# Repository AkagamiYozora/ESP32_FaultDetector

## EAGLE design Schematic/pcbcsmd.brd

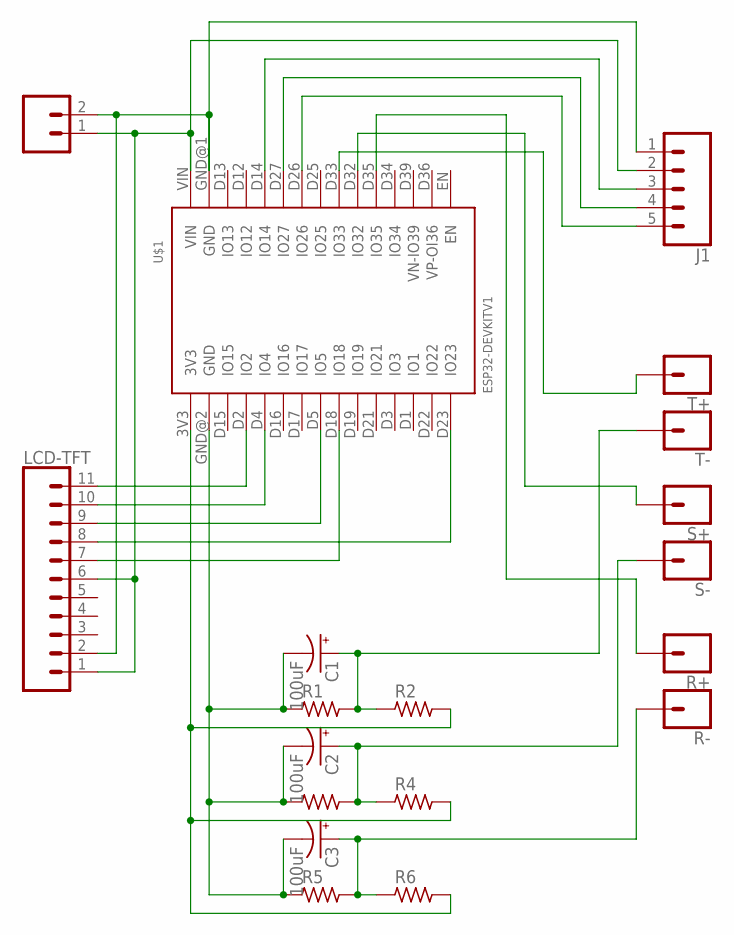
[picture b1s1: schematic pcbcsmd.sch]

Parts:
C1, C2, C3: 100uF; PANASONIC_D
J1: CONN_05; 1X05
LCD-TFT: CONN_11; 1X11
POWER: CONN_02; 1X02
R1, R2, R3, R4, R5, R6: R_0805; R0805
R+: CONN_01; 1X01
R-: CONN_01; 1X01
S+: CONN_01; 1X01
S-: CONN_01; 1X01
T+: CONN_01; 1X01
T-: CONN_01; 1X01
U$1: ESP32DEVKITV1; ESP32-DEVKITV1

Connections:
unnamed: T+.1, U$1.D33 (IO33)
unnamed: R2.2, R4.2, R6.2, U$1.3V3
unnamed: C3.+, R5.2, R6.1, R-.1
unnamed: C2.+, R3.2, R4.1, S-.1
unnamed: C1.+, R1.2, R2.1, T-.1
unnamed: LCD-TFT.11, U$1.D2 (IO2)
unnamed: LCD-TFT.10, U$1.D4 (IO4)
unnamed: C1.-, C2.-, C3.-, R1.1, R3.1, R5.1, U$1.GND@2 (GND)
unnamed: LCD-TFT.7, U$1.D18 (IO18)
unnamed: LCD-TFT.8, U$1.D23 (IO23)
unnamed: S+.1, U$1.D32 (IO32)
unnamed: R+.1, U$1.D35 (IO35)
unnamed: LCD-TFT.9, U$1.D5 (IO5)
unnamed: J1.5, U$1.D26 (IO26)
unnamed: J1.4, U$1.D27 (IO27)
unnamed: J1.3, U$1.D14 (IO14)
unnamed: J1.1, LCD-TFT.2, POWER.2, U$1.GND@1 (GND)
unnamed: J1.2, LCD-TFT.1, LCD-TFT.6, POWER.1, U$1.VIN

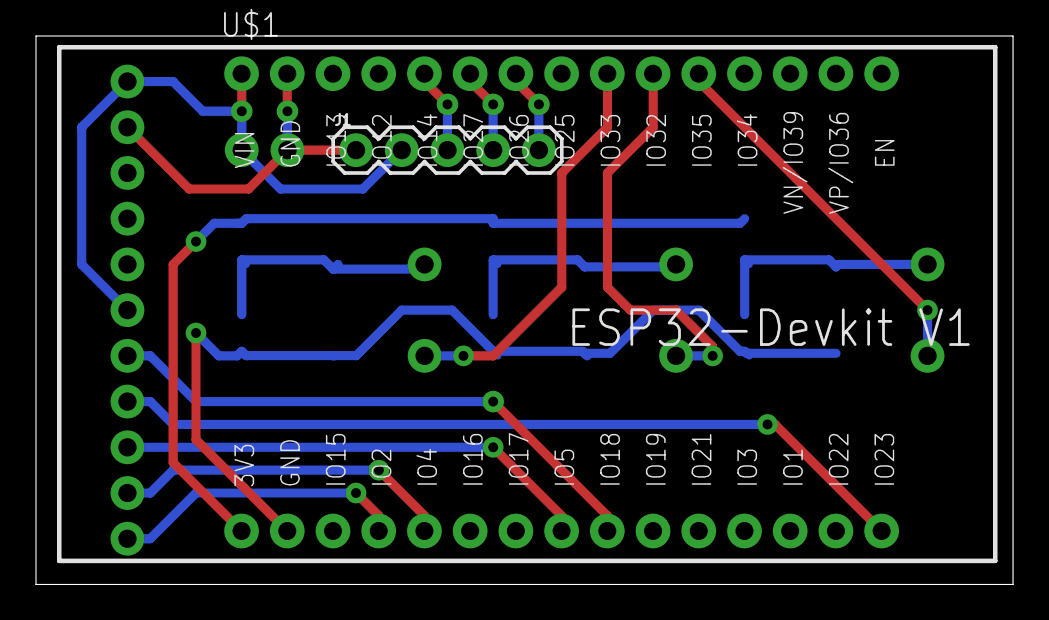
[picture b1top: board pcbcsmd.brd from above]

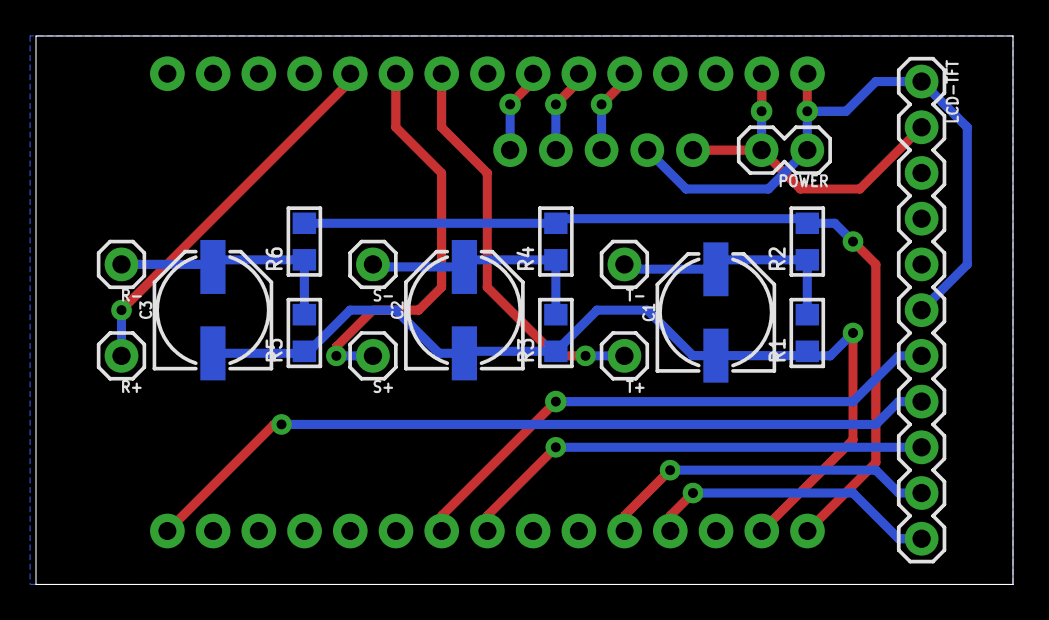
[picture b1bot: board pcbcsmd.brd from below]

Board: 2 copper layers, 54.3 x 30.5 mm, 19 parts (17 on the bottom side), 18 nets.

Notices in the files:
parts and their libraries:
rc-master-smd: Copyright (C) 2007, Bob Starr
SparkFun-Connectors: Licensing: Creative Commons ShareAlike 4.0 International - https://creativecommons.org/licenses/by-sa/4.0
